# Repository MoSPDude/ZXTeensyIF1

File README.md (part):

# ZXTeensyIF1

A Teensy 4.1 powered DivMMC and ZX Interface 1 clone for the ZX Spectrum 48K/128K/+2 (Grey) machines,

* ZX Interface 1
    * Requires the 9V and 5V power rails
    * Uses a MAX232 for the RS232 level shifting, so no +12V or -12V required
    * Supports 16KB shadow soft ROM
        * eg. Ian Collier's modified Interface 1 ROM from https://ftp.nvg.ntnu.no/pub/sinclair/roms/imc-i1rom.zip
            * The [imc-i1.rom](Extras/imc-i1.rom) here contains a copy with the "Parallel Printer" modification disabled
* DivMMC with 512KB RAM
    * Supports accessing the main SD card, HDF and IMG images
    * Supports DivMMC AllRAM extension with write lock, automap disable and alternate MAPRAM page
        * https://github.com/mprato/DivMMC/blob/master/docs/Divmmc_allram_manual.txt
    * Large images over FAT32 file limit can be split into multiple files
        * eg. esximage.hdf, esximage.001, up to esximage.999
        * The maximum SD card image size is ~2TB
    * If you use images from https://esxdos.zxfiles.net/ - remember to hex edit "DMA=1" to "DMA=0"
* Multiface 128 emulation
    * NMI button and soft ROM
* ZX Interface 2 ROM cartridge emulation
    * It does not emulate the Joystick ports
* ZXC2 and ZXC3 with Flash ROM cartridge emulation
    * Implements ZXC2 ROM banking
    * Implements ZXC3 ROM banking with 128KB Flash ROM
    * Implements SPECTRA shadow ROM support
        * The ROM file needs to be named as "SPECTRA_\*.bin"
* Dandanator Mini with Flash ROM cartridge emulation
    * Implements slow pulsed banking, and fast command banking
    * Can load individual MLD files, or full 512KB generated ROM images
* ESP-01S module via TX8/RX8
    * Requires the 9V power rail for the 3.3V regulator
    * Available on ports 0x143B (5179) for RX and 0x133B (4923) for TX
        * https://www.specnext.com/the-next-on-the-network/
    * Optional eLeMeNt ZX ZXi register compatibility for WiFi BIOS 2.0 software
        * Replaces the RTC ports while enabled with the normal UART
        * Supports https://hood.speccy.cz/dwnld/ZXDBdownloader_info.htm
* USB mouse and gamepad Kempston interface
    * Not wired to the board - use a small lead that exits the case
    * eg. StarTech.com "6in USB 2.0 Cable - USB A Female to USB Motherboard 4 Pin Header F/F"
* HDMI output via Raspberry Pi Pico 2 over USB Serial **EXPERIMENTAL**
    * Sends ULA, ULAplus, Timex-video, and AY bus writes to the `Pico2Hdmi` firmware
        * Pico ULA and AY emulation from https://github.com/fruit-bat/pico-zxspectrum
        * Adafruit DVI HSTX video and HDMI audio on the RP2350 HSTX peripheral
    * *NOTE* The Pico 2 firmware code was generated by Codex - based on protocol markdown and existing projects
* RTC module from the Teensy
    * Accessed as a RTC-72421 on ports 0x7X3B
        * The time is only read or written when register 0xD sets HOLD to 1
    * Uses a minor bugfixed RTC.SYS from https://velesoft.speccy.cz/zx/rtcmodule/index.htm
        * Patched byte 6 from 0x0D to 0x7D
    * Can synchronise from WiFi NTP at power on
    * Not persistent, attach a coin cell battery to VBAT
        * See https://www.pjrc.com/store/teensy41.html#timing
* Single speed TZX and TAP playback
    * Playback locks the keyboard, as it overdrives the ULA
    * TAP loading is better done via the DivMMC
* Spectrum +3 uPD765a FDC emulation
    * Integrated lib765 v0.4.2 with additional bug fixes for "EXTENDED" disk loading
    * Requires Spectrum +2A/+3 soft ROM support (see below), or other compatible DOS
* Prism VTX5000 over ESP-01S
    * Creates a serial tunnel over WiFi to given URL
    * Default URL is '"glasstty.com",6502' - https://glasstty.com/telstar/
* Spectrum +3 and ZX LPRINT III Centronics printer
    * Writes output into a timestamped "printer-YYYYMMDD-HHMMSS.txt" file on SD card, adding a numeric suffix if that file already exists
* Soft ROM emulation
    * Override the internal Spectrum ROM with ROMs from SD card
    * Supports 16KB (Spectrum 48K), 32KB (Spectrum 128K/+2 (Grey)) and 64KB (Spectrum +2A/+3) ROMs
        * The +2A/+3 soft ROM support requires port decoding changes (see below)
    * Provides the peripheral ROMs
* Menu ROM derived from TomDDGs ZXPicoIF2Lite ROMExplorer
* Z80 snapshot loading from TomDDGs ZXPicoIF2Lite
    * Integrated "z80torom" for loading 'z80' and 'sna' files
* Save and restore states
    * Uses the Z80 snapshot loader to restore state on power-on
    * Hold the button to disable the power-on restore
* MDR microdrive loading with Paul Farrows SPECTRA Microdrive Emulator
    * http://www.fruitcake.plus.com/Sinclair/Interface2/Cartridges/Interface2_RC_New_Microdrive_Emulator.htm
    * Supports MDR images with up to 90KB of data
* Small WebDAV class 1 HTTP server for WiFi file access over ESP-01S
    * Accepts five clients, with SD card requests processed one at a time
    * Use WinSCP to send files, or HTTP PUT to send files eg. "curl -T FILENAME.ROM http://192.168.0.254/FILENAME.ROM"
        * Includes a simple LOCK/UNLOCK compatibility shim for Windows 11 support
    * Use web browser to list files, and download
* Nihirash's Network Manager for WiFi configuration
    * Small bugfix to clear the BASIC keypress on load
* Velesoft's RTC_SETUP for RTC configuration
    * Minor tweaks to preset the RTC port
* External ROM support
    * ZX Interface 1 edge connector supports other ROM based hardware
    * eg. Retroleum SMART card, real ZX Interface 2 hardware etc.

The ZX Interface 1 v2 ROM is included in compiled firmware, and as noted on other
sources "Amstrad have kindly given their permission for the redistribution
of their copyrighted material but retain that copyright"

The ZXTEENSY directory contains the peripheral ROM images - the exact redistribution
status of these is unknown, but they have been gathered from sources from the Internet,
and provided for convenience and safe-keeping.

This is a project that I started with a view of wanting a DivMMC clone that works with a
ZX Interface 1 attached to my ZX Max 128 - as I own a ZX Microdrive as well as a ZXPicoMD
(https://github.com/TomDDG/ZXPicoMD) ... and didn't want to keep disconnecting the ZX
Interface 1.

> [!WARNING]
> I created this for myself, and it is distributed in the hope that it will be useful,
> but WITHOUT ANY WARRANTY; without even the implied warranty of MERCHANTABILITY or
> FITNESS FOR A PARTICULAR PURPOSE.
>
> I take ZERO responsibility if it damages your hardware!

## Credits

Full credits to the following projects - this project gathers and integrates from
many various sources.

It borrows content, ideas and inspiration from,

* http://www.pjrc.com/teensy/
    * Teensyduino Core and SdFat libraries - provides all the Teensy 4.1 functionality
    * Reused parts of code for the RTC, SDHC and UART drivers
* https://github.com/SensoriumEmbedded/TeensyROM
    * Initial code and parts for the Teensy 4.1 firmware
* https://github.com/TomDDG/ZXPicoIF2Lite
    * ROM menu source code, Z80 snapshot loader, and the idea of a soft ROM
* http://www.fruitcake.plus.com/Sinclair/Interface2/Cartridges/Interface2_RC_Cartridges.htm
    * ZXC2 and ZXC3 banking, and Microdrive Emulator
* http://www.dandare.es/Proyectos_Dandare/ZX_Dandanator%21_Mini_EN.html
    * Dandantor Mini slow banking from PIC source code
    * Also, https://github.com/chernandezba/zesarux/tree/main/src/storage for fast banking
* https://github.com/nihirash/netman-zx
    * WiFi Network Manager for the ESP-01S
* https://velesoft.speccy.cz/zx/rtcmodule/index.htm
    * RTC_SETUP for the RTC module
    * RTC.SYS for EsxDOS
* https://www.seasip.info/Unix/LibDsk/
    * lib765 FDC controller library
* https://github.com/joepasquariello/FlasherX
    * Teensy 4.x OTA upgrade library
* https://github.com/liveboxandy/ZX-Interface-1-Recreated
    * Re-used the ZX Interface 1 board layout and schematic
* https://github.com/ZXSpectrumVault/rom-disassemblies
    * ZX Interface 1 v2 ROM disassembly
* https://spectrumcomputing.co.uk/pub/sinclair/technical-docs/ZXInterface1_Schematics.gif
    * ZX Interface 1 schematic
* https://spectrumcomputing.co.uk/pub/sinclair/technical-docs/PrismVTX5000Modem_Schematics-Interface.bmp
    * Prism VTX5000 schematic
* https://zxpress.ru/chapters_images/periferiya/periferiya-33.png
    * ZX LPRINT III schematic
* https://divide.speccy.cz/files/pgm_model.txt
    * DivIDE programming model
* https://www.thingiverse.com/thing:6500064
    * Also from TomDDG, a replacement ZX Interface 1 case
* https://github.com/fruit-bat/pico-zxspectrum
    * Pico 2 Spectrum ULA and AY emulation
* https://github.com/adafruit/Adafruit-DVI-HSTX
    * Adafruit PiCowBell HSTX DVI Output library and hardware

Without the above projects, this would not have been possible!

## Construction

[Construction details are here](PCB/README.md)

## SD Card Setup

* ZXTEENSY/
    * CONFIGS/
        * \<NAME\>.CFG (Saved configurations that appear as "NAME" in the Menu ROM for quick selection)
    * STATE/\<SLOT\>/ (Save slots 0-14; slot 15 is reserved)
        * STATE.Z80 (Z80 v3 snapshot for the save state)
        * SCREEN.SCR (6912-byte active Spectrum screen for load preview)
        * (Additional saved state files for the save slot)
    * MENU.ROM
    * MF128.ROM (MD5SUM: ca8c9d97c8aedd718d1081fad2e3af8d)
    * GENIE128.ROM (MD5SUM: b942f2e658d15da9747791a15a9a110d)
        * Genie 128K disassembler Multiface 128 RAM image
    * ESXMMC.BIN (MD5SUM: fa50b0258e52b8d72bd83cc2fb6e1013)
    * SPECTRA_IF1_ED2_ME_ROM_Formatted.bin (MD5SUM: 052ad91ee822604960e8ca8d32a3ddb9)
    * IF1.ROM (Optional)
    * VTX.ROM (MD5SUM: 12a62cb7ea7383f109c2711dfca99f5e)
    * LPRINT32.ROM (MD5SUM: e85f4ccb4cc80aaa81cceffb3e064bf7)
    * netman.z80 (WiFi Network Manager snapshot)
    * rtc_setup.z80 (RTC Setup snapshot)
    * ZXTEENSY.CFG (Current configuration from Menu ROM)
* ROMS/
    * (ZX Spectrum ROMs ending ".rom")
    * (ZXC2 ROMs ending ".bin")
    * (Other ROM files)
* (Other ESXDOS files)
* SYS/
    * [RTC.SYS](Extras/RTC.SYS) (Optional, for RTC access)
    * (Other ESXDOS files)
* ZXTEENSY.HEX (Optional, firmware update)

## Using the Menu ROM

To load the Menu ROM, either,

* Use "Boot into Menu" to load on initial power on
* or, Hold the button, and Reset
* or, Hold Reset for longer than 5 seconds

Inside the Menu ROM you can,

* Restart with either the ZXTeensyIF1 enabled or disabled
    * Pressing Reset will also reset with the ZXTeensyIF1 enabled
* Browse the SD card to select files to load, or mount
    * Selecting known file extensions will either load or ask to mount
    * Selecting unknown file extensions will ask for an action
    * From the in-game browser, select a POK file and tick one or more trainers
      before selecting "Apply selected trainers"
* Browse the system Soft ROMs in the "ROMS/" directory to load, or set as Soft ROM
    * Double selecting a system Soft ROM will immediately reset into it
* Select a saved configuration to load
    * Double selecting a saved configuration will immediately reset into it
* Edit the configuration
    * Enable or disable the peripherals
    * Eject mounted disks by selecting them
    * Set to fetch time over the WiFI, and set the timezone
    * Load the RTC Setup or WiFi Network Manager snapshots
* Start or stop the HTTP server to transfer files over WiFi

To firmware update, place the ZXTEENSY.HEX file on the root of the SD card and
select the option from the Menu ROM - then wait for the Spectrum to reset
(!! It will take a minute !!).

In "Load ROMS", from the "ROMS/" directory,

| File extension | File type |
|----------------|-----------|
| .rom | System Soft ROM |
| .bin | ZXC2 cartridge |
| Other | ZX Interface 2 cartridge |

In "Browse SD card", in other directories,

| File extension | File type |
|----------------|-----------|
| .rom, .bin | ROM cartridge, or RAM image |
| .z80, .sna | Z80 snapshot |
| .hdf, .img | DivMMC SD card |
| .dsk | Spectrum +3 disk |
| .mdr | ZX Microdrive cartridge |
| .tap, .tzx | Audio cassette |
| .pok | POK trainers (in-game browser only) |
| Other | The menu will ask for an action |

POK trainers are applied by saving a temporary state to reserved slot 15,
patching the selected RAM banks, and immediately restoring that state. POK
trainers that require a prompted value (`256`) are not supported and cannot be
enabled.

### Preparing the SD Card

ESXDOS has trouble loading if it is not "early" on the SD card,

* Format the SD card with FAT32
* Extract ESXDOS on computer, and transfer all directories and ESXMMC.BIN to the SD card
* Transfer the "/ZXTEENSY" directory, with ROMs and CONFIGS
* Create system "/ROMS" directory, and add other ROMs
* Add any other files

#### Fun stuff !!

The https://esxdos.zxfiles.net/ site has a HDF image that can be split using the script
in the tools folder, to use as an SD card image.

 * You will just need to hex edit part of the image file to change the setting "DMA=1" to "DMA=0" !!
 * You can browse the image with 7-Zip to extract the "GAMES.ROM" folder for access to the ROM games

The [MOONR.zip](Extras/MOONR.zip) is a compiled version of Moon Rabbit v1.6 from
https://github.com/nihirash/moon-rabbit-zx with MB03+ serial for the WiFi, but
with the regular Spectrum screen and without the proxy ("-DMB03 -DZXSCR").

The [imc-i1.rom](Extras/imc-i1.rom) is Ian Collier's modified Interface 1 ROM -
place it as "ZXTEENSY/IF1.ROM" to use instead of the internal compiled v2 ROM.

Z80 BBC BASIC for the ZX Spectrum can be downloaded from https://mdfs.net/Software/Spectrum/BBCBasic/ .
Use the 32K combined BBC BASIC and ZX BASIC ROM - placing it in the ROMS folder, and
selecting it as the system ROM.

## Building the firmware

* Setup the Arduino IDE 2.3.6 for the Teensy 4.1
    * "Teensy (for Arduino IDE 2.0.4 or later)" v1.60.0
* Open ZXTeensyIF1\ZXTeensyIF1.ino
* Set Board to Teensy 4.1
* Set Optimize to "Smallest Code with LTO"
* Set CPU Speed to "720 MHz (overclock)"
* Verify and Upload

## Prism VTX5000 support

The VTX5000 over ESP-01S uses the ESP8266 in UART-WiFi passthrough mode after establishing
a connection to a URL over TCP. If the VTX.ROM is provided, then it will load after reset.
The default URL is the TELSTAR Viewdata service at https://glasstty.com/telstar/ .

To access TELSTAR,
 * Press CAPS SHIFT + ENTER to open the menu
 * Press 0 to "Log ON or OFF"
 * Press 1 for "Manual Log ON"
 * Enter the ID "\*\*\*\*\*\*\*\*\*\*" ie. 10 asterixes
 * Read the welcome message, and press ENTER as the "#" key

To navigate, either press numbers to select items, or enter pages in the form of "*800#" :-
 * SYMBOL SHIFT is the "*" key
 * ENTER is the "#" key

## WebDAV class 1 support

The HTTP server accepts five connections. Requests are processed one at a time because the
ESP-01S UART and SD card are shared; an inactive connection remains buffered by the ESP-01S.

Windows 11 sends LOCK and UNLOCK commands when copying files to the server, though not
supported in WebDAV class 1. The server just acknowledges the exclusive file locks, creates
the empty target required by a LOCK on a new path, and accepts refresh and unlock requests -
purely as a compatibility shim. An interrupted transfer can leave its empty target file behind.

WinSCP seems to work fine - you may need to change the preferences to ensure only
a single upload connection.

OpenAI Codex helped to provide the additional WebDAV class 1 implementation over
just the basic HTTP PUT and GET that I'd implemented.

## +2A/+3 soft ROM on Spectrum 128K/+2 (Grey) machines

Spectrum 128K, +2 (Grey) and similar machines (eg. ZX Max 128 Issue 3) require a modification to
support the +2A/+3 soft ROM.

Without it, accesses to the Secondary Memory Control register (0x1FFD) also affect the original
Memory Control register (0x7FFD) due to the partial decoding. (More info at
https://worldofspectrum.org/faq/reference/128kreference.htm)

### Spectrum 128K/+2 (Grey) Memory Control port decoding

The BANK decoding is performed by a PAL10H8 chip, which can be swapped for a GAL16V8 to apply
the "Unrainer/IN 7FFD" fix - see https://spectrumforeveryone.com/technical/applying-the-unrainerin-7ffd-fix-to-128grey-2-machines/ and
Velesoft https://velesoft.speccy.cz/zx/umbrella/umbrella.htm for the original article and files.

Unrainer fixed GAL16V8s with socket and wire can be bought from the Retroleum shop at
https://retroleum.co.uk/.

But, by adding a "BANK = ... & ZA14" term, then the GAL will support the decoding
required for the +2A/+3 soft ROM.

I've placed the updated files in the GAL folder.

* Remove IC29 (Spectrum 128K) / IC7 (Grey +2) - and replace with a socket
    * *Take care of the orientation of the socket!* (The Grey +2 has it pointing downwards)
* On the underside, add a wire from CPU pin 28 to the GAL socket pin 11
* Program the GAL16V8 with GALNEW2A.JED, and fit into socket
    * Again, taking care with the orientation!

### ZX Max 128 Issue 3 Memory Control port decoding

The modification is shown at
https://github.com/DonSuperfo/ZX-Max-128/blob/main/Issue%203/Modify%20for%20%2B3%20ROM.pdf,

* Replace R12 with a 1N4148 diode, with cathode to U9 pin 9
    * So it is the same orientation as D1 that is next to it
* Add a 1N4148 diode from U6 pin 12 to the cathode of the new diode in place of R12
    * This connects "nA14"
* Add a 10K resistor from ground (eg. U9 pin 8) to the cathode of the new diode in place of R12
    * This is the replacement position for R12

## 3rd party Xbox One USB gamepads

You will need to find and add the USB PID:VID code for the controller to the USBHost_t36
library.

In the case of my "8BitDo M30 Wired Controller for Xbox One", under Windows 11
Device Manager, it was the "Xbox Peripherals > Xbox Gaming Device" *NOT* the
(virtual) HID device. Right click the device, select Properties, then Details and
select "Hardware IDs" to find it listed as "USB\VID_2DC8&PID_200A&..."

Once found, add the USB PID:VID code to %LOCALAPPDATA%\Arduino15\packages\teensy\hardware\avr\1.60.0\libraries\USBHost_t36\joystick.cpp,
under JoystickController::pid_vid_mapping ,

* 8BitDo M30 Wired Controller for Xbox One :- \{ 0x2dc8, 0x200a, XBOXONE, false \}

## Experimental HDMI via Pico 2 over USB Serial

Define `HDMI_CDC_OUTPUT` in `ZXTeensyIF1/DefinesZXTeensy.h` to enable the
experimental `Pico2Hdmi` output. The Teensy 4.1 USB host drives the RP2350 on a
Raspberry Pi Pico 2 as an Adafruit TinyUSB CDC Serial device. The Pico firmware
and its build instructions are in [`Pico2Hdmi`](Pico2Hdmi/README.md).

ULA, ULAplus, Timex-video, and AY bus writes are sent as address/data messages, with
consecutive addresses packed into escaped data runs.

The RP2350 emulates the ULA, ULAplus, Timex hi-colour/hi-res modes, and AY, generating
video and sound over HDMI. Beeper sound is averaged into packets of 44.1 kHz unsigned
8-bit beeper PCM, and sent to the Pico.

HDMI requires two fixes to the USBHost_t36 library bundled with Teensy core
1.60.0. Preview and apply them from the repository root:

```powershell
python tools/patch_usbhost_t36.py
python tools/patch_usbhost_t36.py --apply
python tools/patch_usbhost_t36.py --check
```

The script saves original files beside them with a `.zxteensy-hdmi.bak` suffix
and preserves fixes that are already applied. Use `--library PATH` for a different
Arduino installation. Reapply after reinstalling the core, then compile cleanly.

* In `serial.cpp`, retain the busy flag when queuing a partial packet. Otherwise
  a subsequent write can overwrite a buffer while its USB transfer is active.
* In `ehci.cpp`, make `USBDriverTimer::start()` and `stop()` mask only `IRQ_USBHS`,
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
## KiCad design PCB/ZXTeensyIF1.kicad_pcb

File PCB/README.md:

# ZXTeensyIF1 Construction

## Loading the KiCad project

The PCB folder contains a KiCad 9.0.2 project, based on liveboxandy "ZX Interface 1 Recreated" KiCad
7 project. Without that project, I'd have had to spend considerable time getting the board outline
correct, and aligning the sockets etc.

It uses,

* https://github.com/XenGi/teensy_library as teensy_library-master
* https://github.com/XenGi/teensy.pretty as teensy.pretty-master
    * Set XGENGI_TEENSY_LIBRARY path in Symbol Libraries etc.
* https://github.com/sparkfun/SparkFun-KiCad-Libraries
    * Set SPARKFUN_KICAD_LIBRARY path in Symbol Libraries etc.
* https://github.com/nosuz/kicad-symbols-footprints
    * Place as ./nosuz-kicad-symbols-footprints in the project directory

Freerouting (https://github.com/freerouting/freerouting) was used to perform the initial routing,
especially with getting the address and data lines out to the level shifters and the Interface 1
ULA.

## Bill of Materials

| Reference | Qty | Value | Comments |
| --- | --- | --- | --- |
| C1, C2, C7, C8 | 4 | 1uF | Use 0.1uF if U8 is MAX232A, or 0.33uF if MAX3232 |
| C3 | 1 | 100pF | |
| C4 | 1 | 22pF | |
| C5 | 1 | 47nF | |
| C6, C13 | 2 | 47uF 16V | |
| C9, C10, C11, C12 | 4 | 100nF | |
| D1, D2, D3, D9, D11 | 5 | 1N4148 | |
| D4 | 1 | 1N4001 | or 1N400X equivalent |
| D8 | 1 | BZX79CV4V3 | or ZPD4V3 equivalent |
| J1 | 1 | ESP-01S | Optional, for WiFi |
| J3 | 1 | Polou D24V5F3 | Optional, fit if ESP-01S is fitted |
| L1 | 1 | 22uH 0.41A | |
| Q1, Q2 | 2 | BC213C | or BC214C |
| Q3, Q6, Q9 | 3 | BC184C | or BC183 |
| Q4, Q5, Q7, Q8 | 4 | PN2222A | or 2N2222 |
| Q10, Q11 | 2 | ZTX313 | (or BC183 **if reversed**) |
| R1, R3, R5, R11, R12, R14, R24, R25, R31 | 9 | 1K0 | |
| R2, R10, R17, R18 | 4 | 6K8 | |
| R4, R6, R8, R13 | 4 | 3K9 | |
| R7 | 1 | 47R | |
| R9, R16, R21, R26, R27, R33, R36 | 7 | 10K | |
| R15 | 1 | 2K2 | |
| R22, R23, R34 | 3 | 330R | |
| R30 | 1 | 270R | |
| R35 | 1 | 47K | |
| SK1 | 1 | DE9_Receptacle | |
| SK2, SK3 | 2 | 3.5mm Mono Switched Socket | with break contact eg. Cliff CL1384 |
| SK5 | 1 | ZX Spectrum edge connector | Can be difficult - see notes |
| SW1 | 1 | PTH_RA_h7.5mm | 6 x 6mm x 8mm Right Angle |
| U1 | 1 | LA15-302 | ZX Interface 1 ULA - can be LA15-312 or vLA1 |
| U2 | 1 | Teensy4.1 | Teensy 4.1 No Ethernet |
| U3, U5, U6, U7 | 4 | SN74LVC245AN | |
| U4 | 1 | 74HCU04 | |
| U8 | 1 | MAX232 | or MAX232A or MAX3232 |
| X1 | 1 | 8Mhz crystal | |

## Notes

In my build, the 74HCU04, BZX79CV4V3, 8 MHz crystal, 3K9 resistors, inductor
and all connectors came from a donor ZX Interface 1 board. The ULA was a LA15-312
that I had bought to fix the donor originally, before I had the idea to create
this. Removing the ZX Interface 1 edge connector that goes to the ZX Spectrum was
an immense pain - even with gentle heat, I managed to deform and melt the plastic
riser block... it was as though it was glued to the board as well as screwed.

But for my second board, having found another donor that had a ULA that melted the
case, simply removing the screws holding the edge connector riser and de-soldering
was enough - it was removed very easily! The ULA for this board is a replacement
vLA1, that worked after some firmware fixes. Only the connectors and BZX79CV4V3
had been re-used from this donor board.

The ZX Spectrum edge connector riser will sit over Q10, Q11 and C6 - with the top screwhole
sat in between Q10 and Q11. For this reason, ensure they're close to the board with a gap
in between. C6 might have to lean over U4 a little!

## Hardware revisions

* v0.7b PCB
    * *NOT MANUFACTURED*
    * Changed C13 to 47uF
        * The Teensy was not always resetting correctly after power on, so increased this
    * Moved C6 slightly
        * The ZX Spectrum edge connector plastic riser block had a support that just caught the top of it!
        * Hopefully, this slight adjustment will solve that
* v0.7 PCB prototype
    * PCBs have been returned from PCBWay
    * Moved the ROMCS and DataDir output to pins 36 and 37, to free up pins 34 and 35
    * Added an ESP-01S header, and header for 3.3V regulator (eg. Pololu D24V5F3)
        * The ESP-01S can take over 300mA, so requires a separate regulator
        * The Pololu D24V5F3 is a 3.3V 500mA regulator module, available from The Pi Hut
        * I had to re-organise the left side of the board to make room
    * Connected RX8 pin 34 and TX8 pin 35, to the ESP-01S header
* v0.2 PCB prototype
    * First PCBs made, and tested
        * Microdrive, RS232, ZX Net and nROMCS on external edge connector working
        * Firmware updated for new pin layout - soft ROM all working
    * Need to revise some footprints
    * The PCBs had silkscreen that stated v0.1
* v0.1 veroboard prototype (not uploaded)
    * Prototype to test the initial idea
    * Teensy 4.1 and level shifters on Veroboard
        * Soft ROM and Multiface 128 behaviour working
    * Modded ZX Interface 1 to add "nIORQ inhibit" (see below)

## DivMMC and ZX Interface 1 support

Technically, the DivMMC and ZX Interface 1 cannot be active simultaneously. The DivMMC ports and
ZX Interface 1 I/O ports clash directly. (More info at below)

To overcome this, the Teensy drives the nIORQ of the Interface 1 ULA high when the DivMMC is
active. Also, only A3 and A4 have been wired to the Interface 1 ULA, as required for the port
decoding - which helped with the PCB routing. The Teensy provides all the ROM facilities for
the Interface 1 behaviour.

## Updating the ESP-01S

The ESP-01S needs to be running the Non-OS AT firmware that can be downloaded from
https://github.com/espressif/ESP8266_NONOS_SDK .

The current version is SDK v3.0.6 with AT version 1.7.6.0,
```
AT version:1.7.6.0(Jan 24 2022 08:56:02)
SDK version:3.0.6-dev(072755c)
compile time:Jun 17 2024 07:38:00
Bin version(Wroom 02):1.7.6
```

The ZXTeensyIF1 cannot update the firmware, so it needs to be done with a suitable
connection to a computer - such as https://thepihut.com/products/esp-flasher and
the VSCode Serial Monitor.

To find your current version, issue the command "AT+GWR" at baud rate 115200,
1 stop bit, no parity, DTR set, RTS set, with CRLF line endings.

I used esptool-v4.8.1-win64 and the following command to flash, with my USB serial
adapter on COM3,
```
./esptool.exe -p COM3 write_flash --flash_size 1MB 0x0 boot_v1.7.bin 0x01000 user1.1024.new.2.bin 0xfb000 blank.bin 0xfc000 esp_init_data_default_v08.bin 0xfe000 blank.bin 0x7e000 blank.bin
```

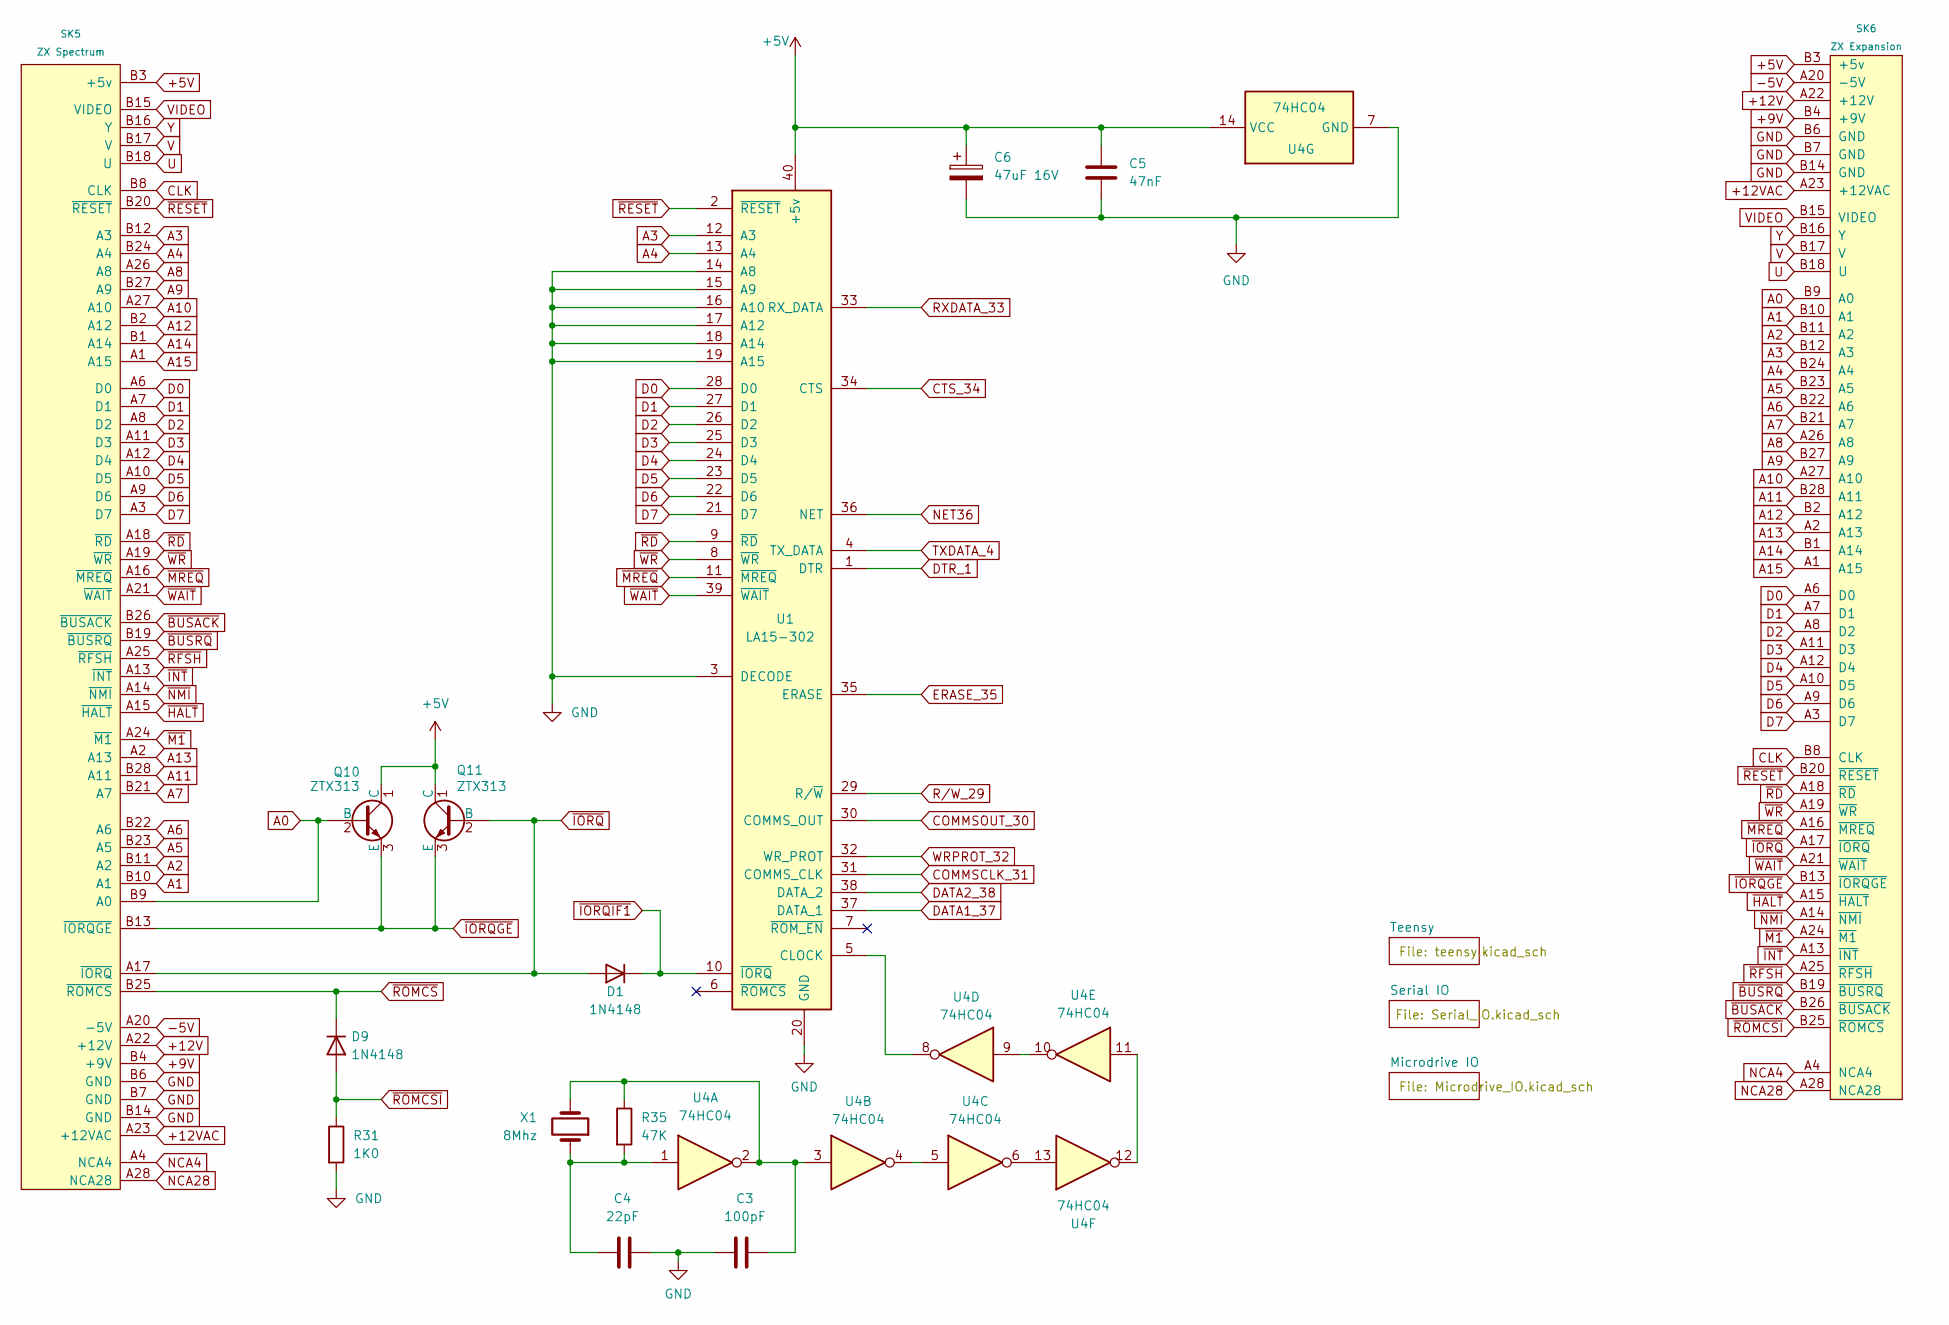
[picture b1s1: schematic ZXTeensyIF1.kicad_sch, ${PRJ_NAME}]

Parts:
C3: 100pF; C_Disc_D3.4mm_W2.1mm_P2.50mm
C4: 22pF; C_Disc_D3.4mm_W2.1mm_P2.50mm
C5: 47nF; C_Disc_D3.4mm_W2.1mm_P2.50mm
C6: 47uF 16V; CP_Radial_D5.0mm_P2.50mm
D1, D9: 1N4148; D_DO-35_SOD27_P7.62mm_Horizontal
Q10, Q11: ZTX313; TO-92L_Inline_Wide
R31: 1K0; R_Axial_DIN0207_L6.3mm_D2.5mm_P7.62mm_Horizontal
R35: 47K; R_Axial_DIN0207_L6.3mm_D2.5mm_P7.62mm_Horizontal
SK5: ZX Spectrum; Spectrum_Edge_Connector
SK6: ZX Expansion; ZX_Bus_Edge_Connector
U1: LA15-302; DIP-40_W15.24mm
U4: 74HC04; DIP-14_W7.62mm
X1: 8Mhz; Crystal_HC18-U_Horizontal

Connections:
+5V: C5.1, C6.1, Q10.1 (C), Q11.1 (C), SK5.B3 (+5v), SK6.B3 (+5v), U1.40 (+5v), U4.14 (VCC); also elsewhere on the board
+9V: SK5.B4 (+9V), SK6.B4 (+9V); also elsewhere on the board
+12V: SK5.A22 (+12V), SK6.A22 (+12V)
+12VAC: SK5.A23 (+12VAC), SK6.A23 (+12VAC)
-5V: SK5.A20 (-5V), SK6.A20 (-5V)
A0: Q10.2 (B), SK5.B9 (A0), SK6.B9 (A0); also elsewhere on the board
A1: SK5.B10 (A1), SK6.B10 (A1); also elsewhere on the board
A2: SK5.B11 (A2), SK6.B11 (A2); also elsewhere on the board
A3: SK5.B12 (A3), SK6.B12 (A3), U1.12 (A3); also elsewhere on the board
A4: SK5.B24 (A4), SK6.B24 (A4), U1.13 (A4); also elsewhere on the board
A5: SK5.B23 (A5), SK6.B23 (A5); also elsewhere on the board
A6: SK5.B22 (A6), SK6.B22 (A6); also elsewhere on the board
A7: SK5.B21 (A7), SK6.B21 (A7); also elsewhere on the board
A8: SK5.A26 (A8), SK6.A26 (A8); also elsewhere on the board
A9: SK5.B27 (A9), SK6.B27 (A9); also elsewhere on the board
A10: SK5.A27 (A10), SK6.A27 (A10); also elsewhere on the board
A11: SK5.B28 (A11), SK6.B28 (A11); also elsewhere on the board
A12: SK5.B2 (A12), SK6.B2 (A12); also elsewhere on the board
A13: SK5.A2 (A13), SK6.A2 (A13); also elsewhere on the board
A14: SK5.B1 (A14), SK6.B1 (A14); also elsewhere on the board
A15: SK5.A1 (A15), SK6.A1 (A15); also elsewhere on the board
CLK: SK5.B8 (CLK), SK6.B8 (CLK)
COMMSCLK_31: U1.31 (COMMS_CLK); also elsewhere on the board
COMMSOUT_30: U1.30 (COMMS_OUT); also elsewhere on the board
CTS_34: U1.34 (CTS); also elsewhere on the board
D0: SK5.A6 (D0), SK6.A6 (D0), U1.28 (D0); also elsewhere on the board
D1: SK5.A7 (D1), SK6.A7 (D1), U1.27 (D1); also elsewhere on the board
D2: SK5.A8 (D2), SK6.A8 (D2), U1.26 (D2); also elsewhere on the board
D3: SK5.A11 (D3), SK6.A11 (D3), U1.25 (D3); also elsewhere on the board
D4: SK5.A12 (D4), SK6.A12 (D4), U1.24 (D4); also elsewhere on the board
D5: SK5.A10 (D5), SK6.A10 (D5), U1.23 (D5); also elsewhere on the board
D6: SK5.A9 (D6), SK6.A9 (D6), U1.22 (D6); also elsewhere on the board
D7: SK5.A3 (D7), SK6.A3 (D7), U1.21 (D7); also elsewhere on the board
DATA1_37: U1.37 (DATA_1); also elsewhere on the board
DATA2_38: U1.38 (DATA_2); also elsewhere on the board
DTR_1: U1.1 (DTR); also elsewhere on the board
ERASE_35: U1.35 (ERASE); also elsewhere on the board
GND: C3.2, C4.1, C5.2, C6.2, R31.2, SK5.B6 (GND), SK5.B7 (GND), SK5.B14 (GND), SK6.B6 (GND), SK6.B7 (GND), SK6.B14 (GND), U1.3 (DECODE), U1.14 (A8), U1.15 (A9), U1.16 (A10), U1.17 (A12), U1.18 (A14), U1.19 (A15), U1.20 (GND), U4.7 (GND); also elsewhere on the board
NCA4: SK5.A4 (NCA4), SK6.A4 (NCA4)
NCA28: SK5.A28 (NCA28), SK6.A28 (NCA28)
NET36: U1.36 (NET); also elsewhere on the board
unnamed: C3.1, R35.1, U4.2, U4.3, X1.2
unnamed: C4.2, R35.2, U4.1, X1.1
unnamed: U1.5 (CLOCK), U4.8
unnamed: U4.4, U4.5
unnamed: U4.9, U4.10
unnamed: U4.11, U4.12
unnamed: U4.6, U4.13
RXDATA_33: U1.33 (RX_DATA); also elsewhere on the board
R/W_29: U1.29 (R/~W); also elsewhere on the board
TXDATA_4: U1.4 (TX_DATA); also elsewhere on the board
U: SK5.B18 (U), SK6.B18 (U)
V: SK5.B17 (V), SK6.B17 (V)
VIDEO: SK5.B15 (VIDEO), SK6.B15 (VIDEO)
WRPROT_32: U1.32 (WR_PROT); also elsewhere on the board
Y: SK5.B16 (Y), SK6.B16 (Y)
~BUSACK: SK5.B26 (~BUSACK), SK6.B26 (~BUSACK)
~BUSRQ: SK5.B19 (~BUSRQ), SK6.B19 (~BUSRQ)
~HALT: SK5.A15 (~HALT), SK6.A15 (~HALT)
~INT: SK5.A13 (~INT), SK6.A13 (~INT)
~IORQGE: Q10.3 (E), Q11.3 (E), SK5.B13 (~IORQGE), SK6.B13 (~IORQGE)
~IORQIF1: D1.1 (K), U1.10 (~IORQ); also elsewhere on the board
~IORQ: D1.2 (A), Q11.2 (B), SK5.A17 (~IORQ), SK6.A17 (~IORQ); also elsewhere on the board
~M1: SK5.A24 (~M1), SK6.A24 (~M1); also elsewhere on the board
~MREQ: SK5.A16 (~MREQ), SK6.A16 (~MREQ), U1.11 (~MREQ); also elsewhere on the board
~NMI: SK5.A14 (~NMI), SK6.A14 (~NMI); also elsewhere on the board
~RD: SK5.A18 (~RD), SK6.A18 (~RD), U1.9 (~RD); also elsewhere on the board
~RESET: SK5.B20 (~RESET), SK6.B20 (~RESET), U1.2 (~RESET); also elsewhere on the board
~RFSH: SK5.A25 (~RFSH), SK6.A25 (~RFSH)
~ROMCSI: D9.2 (A), R31.1, SK6.B25 (~ROMCS); also elsewhere on the board
~ROMCS: D9.1 (K), SK5.B25 (~ROMCS); also elsewhere on the board
~WAIT: SK5.A21 (~WAIT), SK6.A21 (~WAIT), U1.39 (~WAIT)
~WR: SK5.A19 (~WR), SK6.A19 (~WR), U1.8 (~WR); also elsewhere on the board

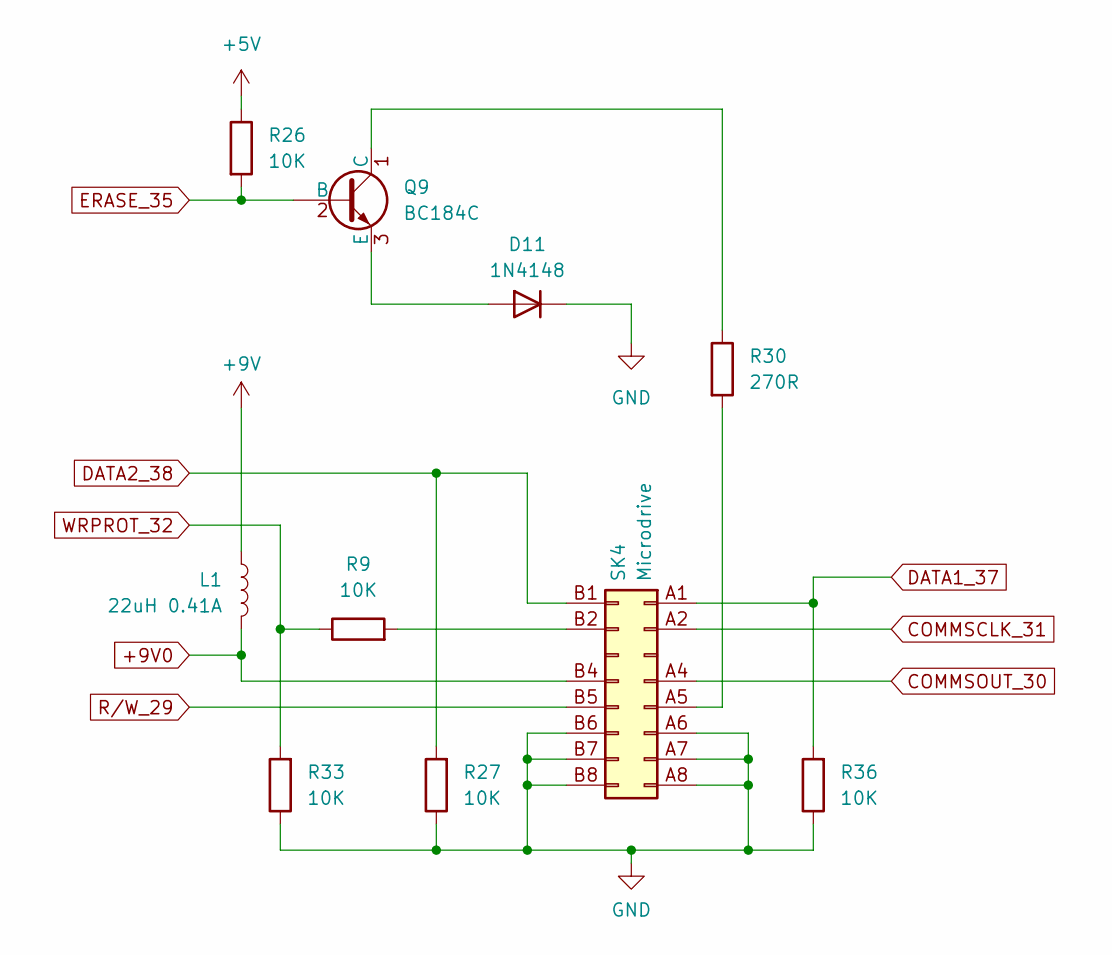
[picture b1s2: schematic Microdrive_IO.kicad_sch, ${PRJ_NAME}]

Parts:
D11: 1N4148; D_DO-35_SOD27_P7.62mm_Horizontal
L1: 22uH 0.41A; L_Axial_L12.8mm_D5.8mm_P20.32mm_Horizontal_Fastron_HBCC
Q9: BC184C; TO-92L_Inline_Wide
R9, R26, R27, R33, R36: 10K; R_Axial_DIN0207_L6.3mm_D2.5mm_P10.16mm_Horizontal
R30: 270R; R_Axial_DIN0207_L6.3mm_D2.5mm_P10.16mm_Horizontal
SK4: Microdrive; ZX_MD_Edge_Connector

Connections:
+5V: R26.1; also elsewhere on the board
+9V: L1.1; also elsewhere on the board
+9V0: L1.2, SK4.B4; also elsewhere on the board
COMMSCLK_31: SK4.A2; also elsewhere on the board
COMMSOUT_30: SK4.A4; also elsewhere on the board
DATA1_37: R36.2, SK4.A1; also elsewhere on the board
DATA2_38: R27.2, SK4.B1; also elsewhere on the board
ERASE_35: Q9.2 (B), R26.2; also elsewhere on the board
GND: D11.1 (K), R27.1, R33.1, R36.1, SK4.A6, SK4.A7, SK4.A8, SK4.B6, SK4.B7, SK4.B8; also elsewhere on the board
unnamed: D11.2 (A), Q9.3 (E)
unnamed: Q9.1 (C), R30.1
unnamed: R30.2, SK4.A5
unnamed: R9.2, SK4.B2
R/W_29: SK4.B5; also elsewhere on the board
WRPROT_32: R9.1, R33.2; also elsewhere on the board

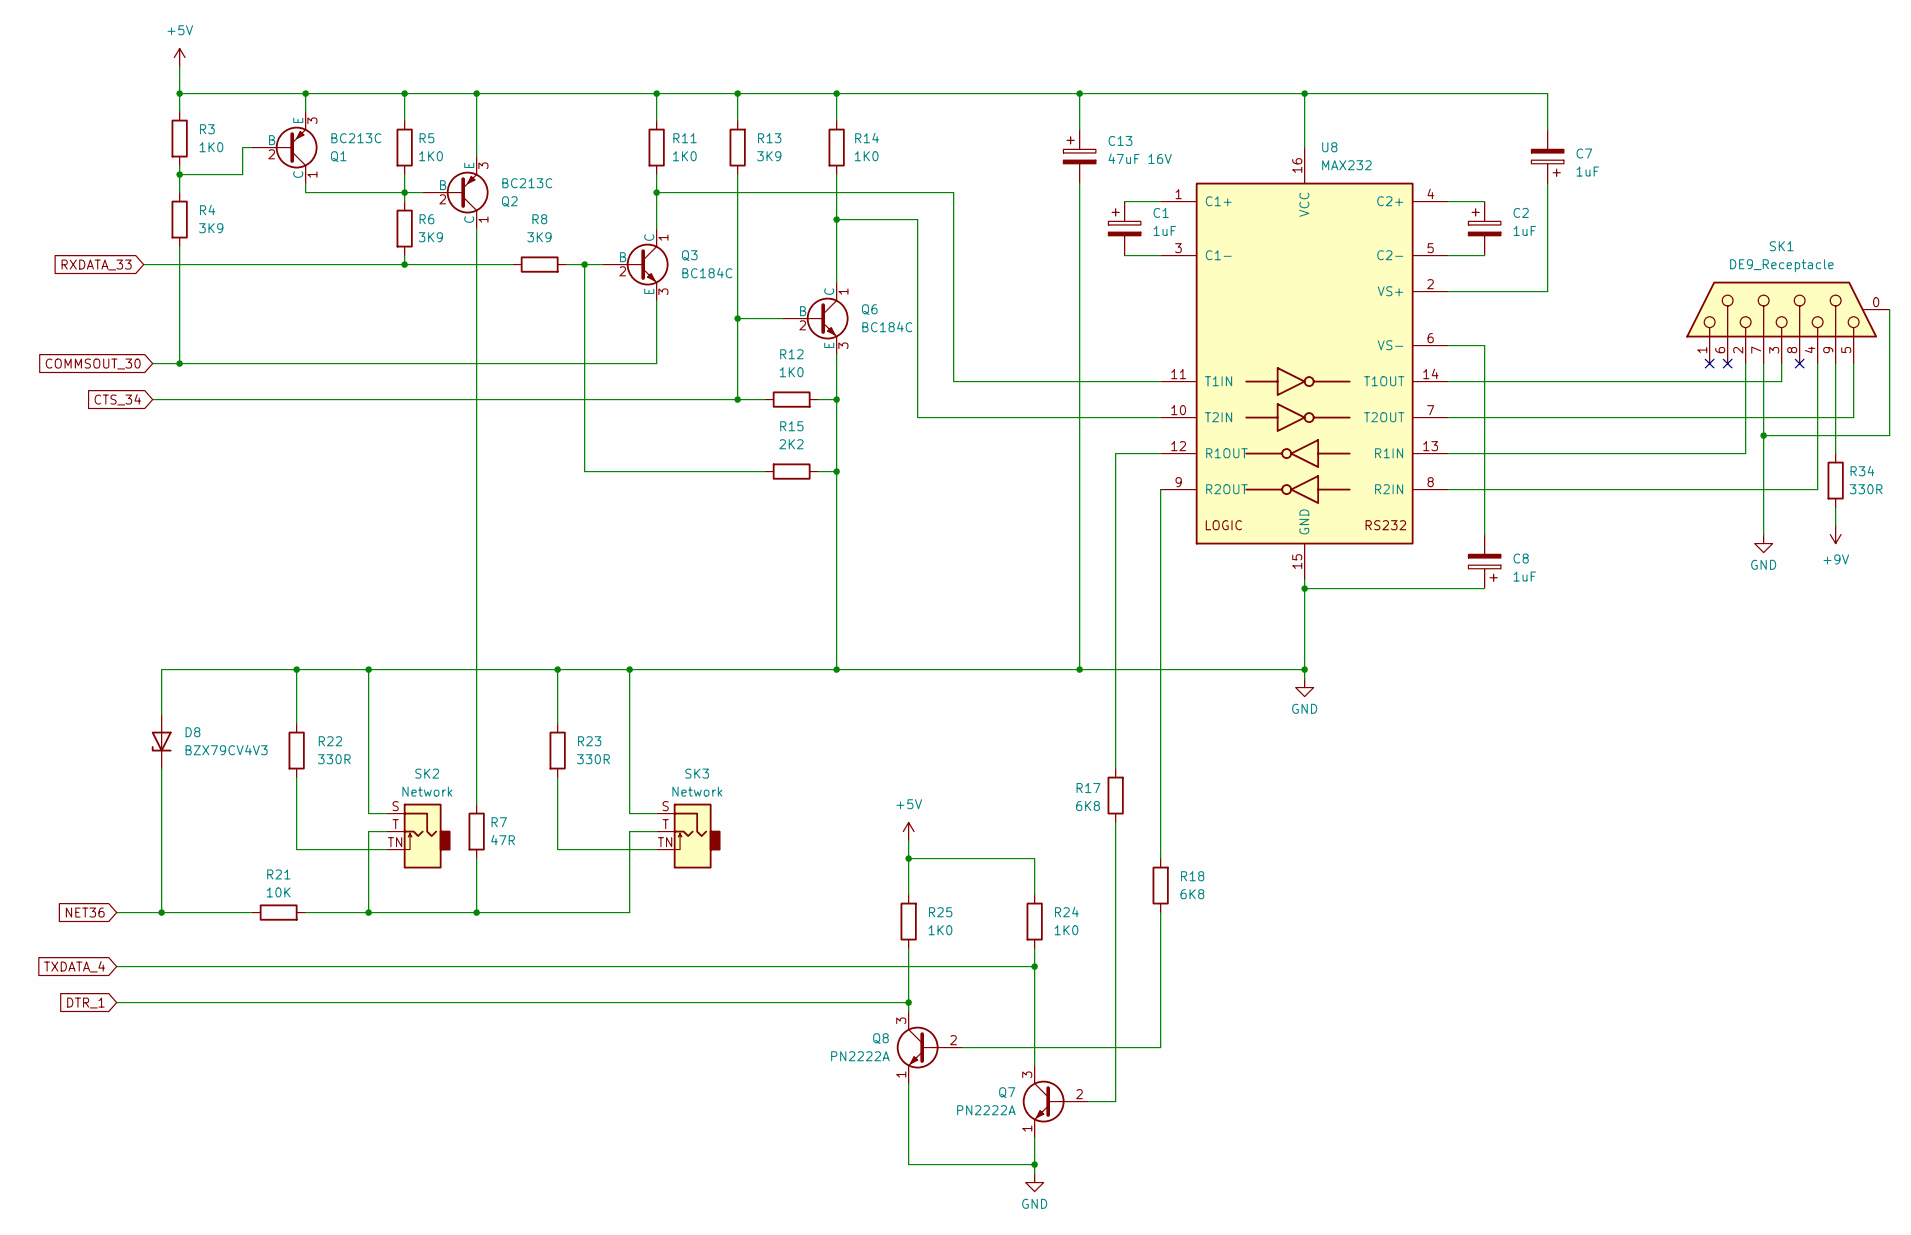
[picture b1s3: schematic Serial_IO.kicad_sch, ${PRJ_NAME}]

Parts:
C1, C2, C7, C8: 1uF; CP_Radial_D5.0mm_P2.50mm
C13: 47uF 16V; CP_Radial_D5.0mm_P2.50mm
D8: BZX79CV4V3; D_DO-35_SOD27_P10.16mm_Horizontal
Q1, Q2: BC213C; TO-92L_Inline_Wide
Q3, Q6: BC184C; TO-92L_Inline_Wide
Q7, Q8: PN2222A; TO-92_Inline_Wide
R3, R5, R11, R12, R14, R24, R25: 1K0; R_Axial_DIN0207_L6.3mm_D2.5mm_P10.16mm_Horizontal
R4, R6, R8, R13: 3K9; R_Axial_DIN0207_L6.3mm_D2.5mm_P10.16mm_Horizontal
R7: 47R; R_Axial_DIN0207_L6.3mm_D2.5mm_P10.16mm_Horizontal
R15: 2K2; R_Axial_DIN0207_L6.3mm_D2.5mm_P10.16mm_Horizontal
R17, R18: 6K8; R_Axial_DIN0207_L6.3mm_D2.5mm_P10.16mm_Horizontal
R21: 10K; R_Axial_DIN0207_L6.3mm_D2.5mm_P10.16mm_Horizontal
R22, R23, R34: 330R; R_Axial_DIN0207_L6.3mm_D2.5mm_P10.16mm_Horizontal
SK1: DE9_Receptacle; DSUB-9_Socket_Horizontal_P2.77x2.84mm_EdgePinOffset14.56mm_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
SK2, SK3: Network; ZX Spectrum 3.5mm Skt
U8: MAX232; DIP-16_W7.62mm

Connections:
+5V: C7.2, C13.1, Q1.3 (E), Q2.3 (E), R3.1, R5.1, R11.1, R13.2, R14.1, R24.1, R25.2, U8.16 (VCC); also elsewhere on the board
+9V: R34.2; also elsewhere on the board
COMMSOUT_30: Q3.3 (E), R4.2; also elsewhere on the board
CTS_34: Q6.2 (B), R12.1, R13.1; also elsewhere on the board
DTR_1: Q8.3 (C), R25.1; also elsewhere on the board
GND: C8.1, C13.2, D8.2 (A), Q6.3 (E), Q7.1 (E), Q8.1 (E), R12.2, R15.1, R22.1, R23.1, SK1.0 (PAD), SK1.7, SK2.S, SK3.S, U8.15 (GND); also elsewhere on the board
NET36: D8.1 (K), R21.1; also elsewhere on the board
unnamed: Q1.2 (B), R3.2, R4.1
unnamed: Q1.1 (C), Q2.2 (B), R5.2, R6.1
unnamed: Q2.1 (C), R7.1
unnamed: Q3.2 (B), R8.2, R15.2
unnamed: Q3.1 (C), R11.2, U8.11 (T1IN)
unnamed: Q6.1 (C), R14.2, U8.10 (T2IN)
unnamed: Q7.2 (B), R17.1
unnamed: Q8.2 (B), R18.1
unnamed: R7.2, R21.2, SK2.T, SK3.T
unnamed: R22.2, SK2.TN
unnamed: R23.2, SK3.TN
unnamed: R34.1, SK1.9
unnamed: C1.1, U8.1 (C1+)
unnamed: C1.2, U8.3 (C1-)
unnamed: C2.1, U8.4 (C2+)
unnamed: C2.2, U8.5 (C2-)
unnamed: SK1.2, U8.13 (R1IN)
unnamed: R17.2, U8.12 (R1OUT)
unnamed: SK1.4, U8.8 (R2IN)
unnamed: R18.2, U8.9 (R2OUT)
unnamed: SK1.3, U8.14 (T1OUT)
unnamed: SK1.5, U8.7 (T2OUT)
unnamed: C7.1, U8.2 (VS+)
unnamed: C8.2, U8.6 (VS-)
RXDATA_33: R6.2, R8.1; also elsewhere on the board
TXDATA_4: Q7.3 (C), R24.2; also elsewhere on the board

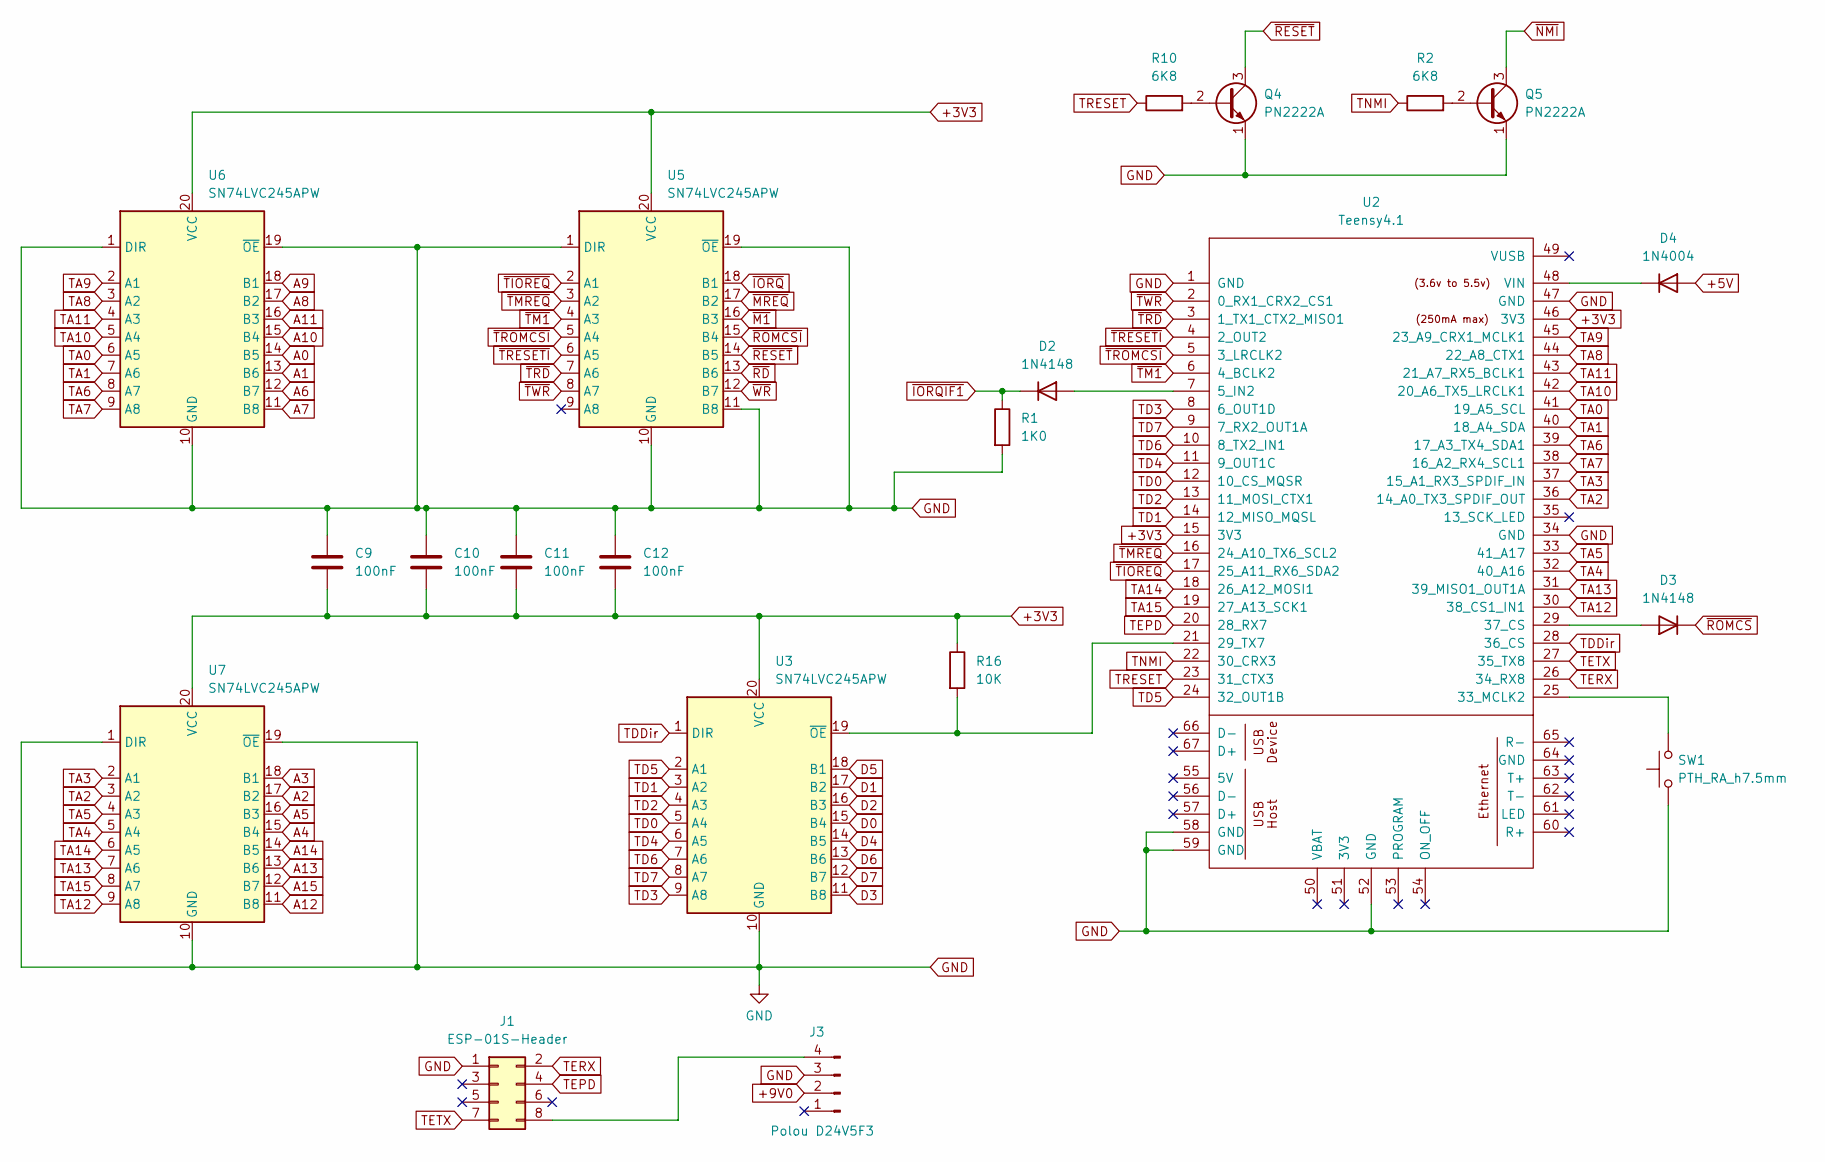
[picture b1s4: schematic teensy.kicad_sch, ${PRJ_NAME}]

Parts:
C9, C10, C11, C12: 100nF; C_Disc_D3.4mm_W2.1mm_P2.50mm
D2, D3: 1N4148; D_DO-35_SOD27_P7.62mm_Horizontal
D4: 1N4004; D_DO-41_SOD81_P10.16mm_Horizontal
J1: ESP-01S-Header; PinSocket_2x04_P2.54mm_Vertical
J3: Polou D24V5F3; PinSocket_1x04_P2.54mm_Vertical
Q4, Q5: PN2222A; TO-92_Inline_Wide
R1: 1K0; R_Axial_DIN0207_L6.3mm_D2.5mm_P7.62mm_Horizontal
R2, R10: 6K8; R_Axial_DIN0207_L6.3mm_D2.5mm_P7.62mm_Horizontal
R16: 10K; R_Axial_DIN0207_L6.3mm_D2.5mm_P10.16mm_Horizontal
SW1: PTH_RA_h7.5mm; Push_PTH_RA_8-020_h7.5mm; Mfg Part# 8-020 TS H = 7.5mm
U2: Teensy4.1; Teensy41
U3, U5, U6, U7: SN74LVC245APW; DIP-20_W7.62mm

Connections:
+3V3: C9.2, C10.2, C11.2, C12.2, R16.1, U2.15 (3V3), U2.46 (3V3), U3.20 (VCC), U5.20 (VCC), U6.20 (VCC), U7.20 (VCC)
+5V: D4.2 (A); also elsewhere on the board
+9V0: J3.2; also elsewhere on the board
A0: U6.14 (B5); also elsewhere on the board
A1: U6.13 (B6); also elsewhere on the board
A2: U7.17 (B2); also elsewhere on the board
A3: U7.18 (B1); also elsewhere on the board
A4: U7.15 (B4); also elsewhere on the board
A5: U7.16 (B3); also elsewhere on the board
A6: U6.12 (B7); also elsewhere on the board
A7: U6.11 (B8); also elsewhere on the board
A8: U6.17 (B2); also elsewhere on the board
A9: U6.18 (B1); also elsewhere on the board
A10: U6.15 (B4); also elsewhere on the board
A11: U6.16 (B3); also elsewhere on the board
A12: U7.11 (B8); also elsewhere on the board
A13: U7.13 (B6); also elsewhere on the board
A14: U7.14 (B5); also elsewhere on the board
A15: U7.12 (B7); also elsewhere on the board
D0: U3.15 (B4); also elsewhere on the board
D1: U3.17 (B2); also elsewhere on the board
D2: U3.16 (B3); also elsewhere on the board
D3: U3.11 (B8); also elsewhere on the board
D4: U3.14 (B5); also elsewhere on the board
D5: U3.18 (B1); also elsewhere on the board
D6: U3.13 (B6); also elsewhere on the board
D7: U3.12 (B7); also elsewhere on the board
GND: C9.1, C10.1, C11.1, C12.1, J1.1, J3.3, Q4.1 (E), Q5.1 (E), R1.2, SW1.1, U2.1 (GND), U2.34 (GND), U2.47 (GND), U2.52 (GND), U2.58 (GND), U2.59 (GND), U3.10 (GND), U5.1 (DIR), U5.10 (GND), U5.11 (B8), U5.19 (~OE), U6.1 (DIR), U6.10 (GND), U6.19 (~OE), U7.1 (DIR), U7.10 (GND), U7.19 (~OE); also elsewhere on the board
unnamed: D2.2 (A), U2.7 (5_IN2)
unnamed: D3.2 (A), U2.29 (37_CS)
unnamed: D4.1 (K), U2.48 (VIN)
unnamed: J1.8, J3.4
unnamed: Q4.2 (B), R10.2
unnamed: Q5.2 (B), R2.2
unnamed: R16.2, U2.21 (29_TX7), U3.19 (~OE)
unnamed: SW1.2, U2.25 (33_MCLK2)
TA0: U2.41 (19_A5_SCL), U6.6 (A5)
TA1: U2.40 (18_A4_SDA), U6.7 (A6)
TA2: U2.36 (14_A0_TX3_SPDIF_OUT), U7.3 (A2)
TA3: U2.37 (15_A1_RX3_SPDIF_IN), U7.2 (A1)
TA4: U2.32 (40_A16), U7.5 (A4)
TA5: U2.33 (41_A17), U7.4 (A3)
TA6: U2.39 (17_A3_TX4_SDA1), U6.8 (A7)
TA7: U2.38 (16_A2_RX4_SCL1), U6.9 (A8)
TA8: U2.44 (22_A8_CTX1), U6.3 (A2)
TA9: U2.45 (23_A9_CRX1_MCLK1), U6.2 (A1)
TA10: U2.42 (20_A6_TX5_LRCLK1), U6.5 (A4)
TA11: U2.43 (21_A7_RX5_BCLK1), U6.4 (A3)
TA12: U2.30 (38_CS1_IN1), U7.9 (A8)
TA13: U2.31 (39_MISO1_OUT1A), U7.7 (A6)
TA14: U2.18 (26_A12_MOSI1), U7.6 (A5)
TA15: U2.19 (27_A13_SCK1), U7.8 (A7)
TD0: U2.12 (10_CS_MQSR), U3.5 (A4)
TD1: U2.14 (12_MISO_MQSL), U3.3 (A2)
TD2: U2.13 (11_MOSI_CTX1), U3.4 (A3)
TD3: U2.8 (6_OUT1D), U3.9 (A8)
TD4: U2.11 (9_OUT1C), U3.6 (A5)
TD5: U2.24 (32_OUT1B), U3.2 (A1)
TD6: U2.10 (8_TX2_IN1), U3.7 (A6)
TD7: U2.9 (7_RX2_OUT1A), U3.8 (A7)
TDDir: U2.28 (36_CS), U3.1 (DIR)
TEPD: J1.4, U2.20 (28_RX7)
TERX: J1.2, U2.26 (34_RX8)
TETX: J1.7, U2.27 (35_TX8)
TNMI: R2.1, U2.22 (30_CRX3)
TRESET: R10.1, U2.23 (31_CTX3)
~IORQIF1: D2.1 (K), R1.1; also elsewhere on the board
~IORQ: U5.18 (B1); also elsewhere on the board
~M1: U5.16 (B3); also elsewhere on the board
~MREQ: U5.17 (B2); also elsewhere on the board
~NMI: Q5.3 (C); also elsewhere on the board
~RD: U5.13 (B6); also elsewhere on the board
~RESET: Q4.3 (C), U5.14 (B5); also elsewhere on the board
~ROMCSI: U5.15 (B4); also elsewhere on the board
~ROMCS: D3.1 (K); also elsewhere on the board
~TIOREQ: U2.17 (25_A11_RX6_SDA2), U5.2 (A1)
~TM1: U2.6 (4_BCLK2), U5.4 (A3)
~TMREQ: U2.16 (24_A10_TX6_SCL2), U5.3 (A2)
~TRD: U2.3 (1_TX1_CTX2_MISO1), U5.7 (A6)
~TRESETI: U2.4 (2_OUT2), U5.6 (A5)
~TROMCSI: U2.5 (3_LRCLK2), U5.5 (A4)
~TWR: U2.2 (0_RX1_CRX2_CS1), U5.8 (A7)
~WR: U5.12 (B7); also elsewhere on the board
